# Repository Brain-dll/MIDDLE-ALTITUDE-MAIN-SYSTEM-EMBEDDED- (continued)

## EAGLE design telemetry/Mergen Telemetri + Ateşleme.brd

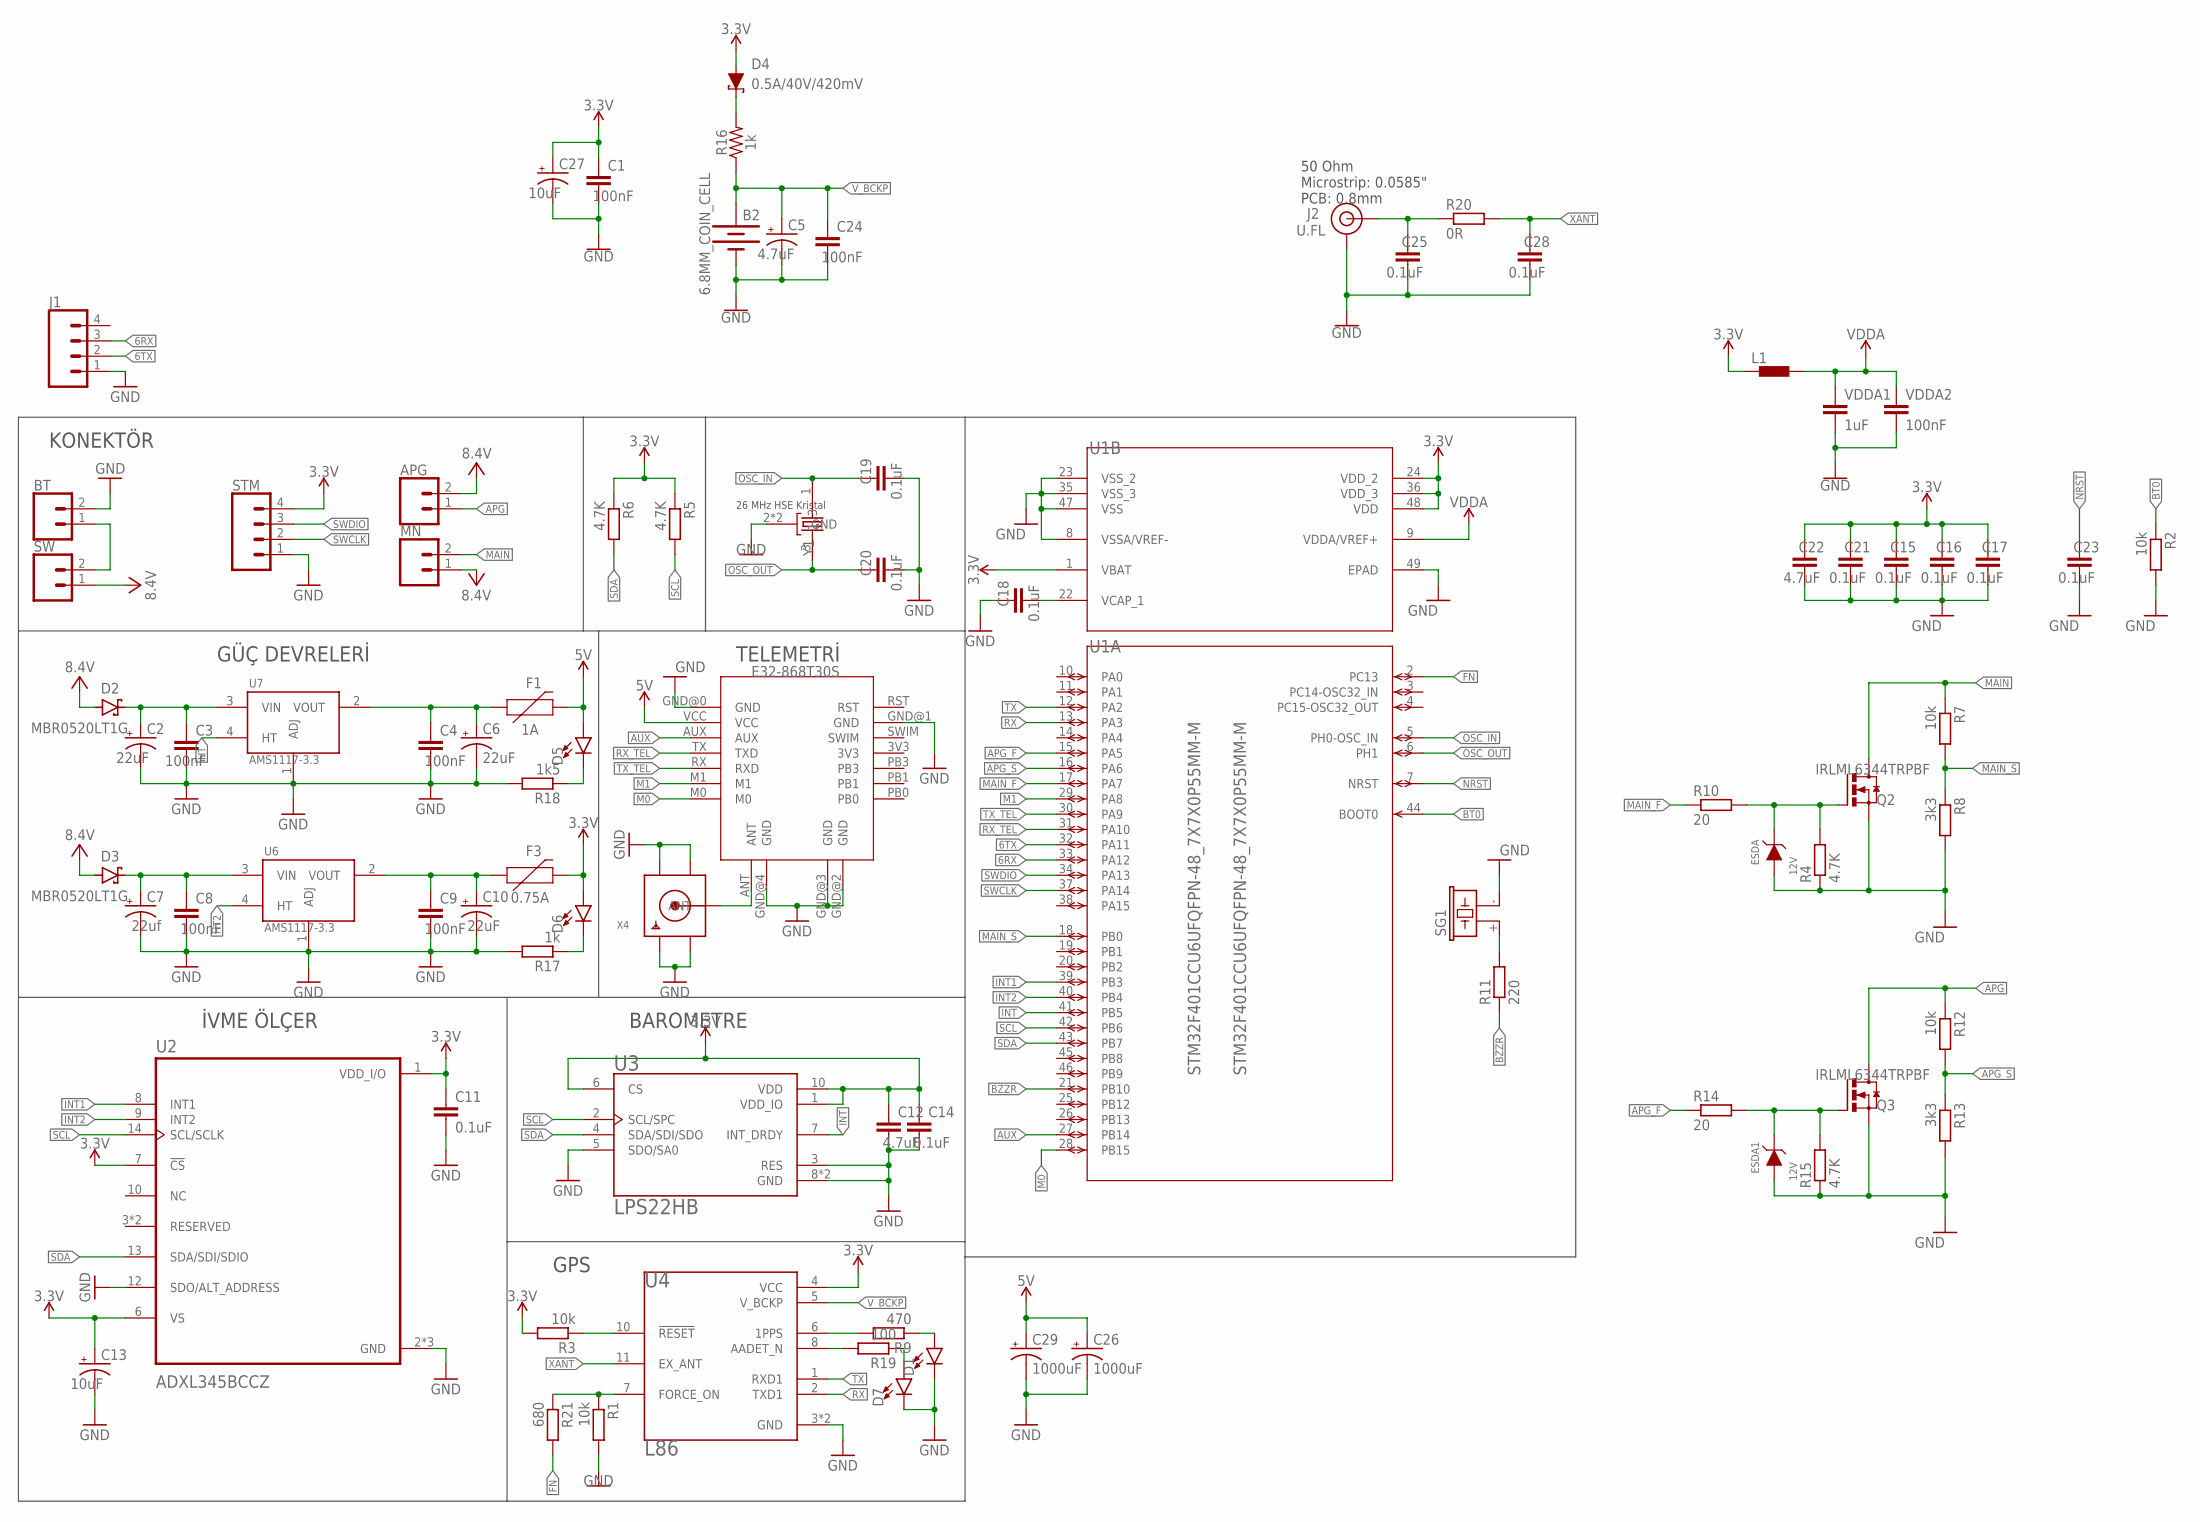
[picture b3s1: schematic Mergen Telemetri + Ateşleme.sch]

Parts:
APG: CONN_02POLAR; MOLEX-1X2
B2: 6.8MM_COIN_CELL; BATTCON-6.8MM
BT: CONN_02POLAR; MOLEX-1X2
C1, C3, C4, C8, C9, C24: 100nF; C0402K
C2, C6, C10: 22uF; R/2012-12W
C5: 4.7uF; R/2012-12W
C7: 22uf; R/2012-12W
C11, C14, C15, C16, C17, C18, C19, C20, C21, C23, C25, C28: 0.1uF; C0402K
C12, C22: 4.7uF; C0402K
C13, C27: 10uF; R/2012-12W
C26, C29: 1000uF; 150CLZ-1010
D1, D5, D6, D7: LED0603; LED-0603
D2, D3: MBR0520LT1G; SODFL3718X115
D4: 0.5A/40V/420mV; SOD-323
ESDA, ESDA1: 12V; WE-TVSP_DO-214AC_UNIDIRECTIONAL
F1: 1A; 1206
F3: 0.75A; 1206
J1: CONN_04JST-PTH-VERT; JST-4-PTH-VERT
J2: U.FL
L1: BLM15HB221SN1; 0402
MN: CONN_02POLAR; MOLEX-1X2
Q2, Q3: IRLML6344TRPBF; SOT23
R1, R2, R3, R7, R12: 10k; R0402
R4, R5, R6, R15: 4.7K; R0402
R8, R13: 3k3; R0402
R9: 470; R0402
R10, R14: 20; R0402
R11: 220; R0402
R16: 1k; 0603
R17: 1k; R0402
R18: 1k5; R0402
R19: 100; R0402
R20: 0R; R0402
R21: 680; R0402
SG1: F/CM12P
STM: CONN_04; 1X04
SW: CONN_02POLAR; MOLEX-1X2
U1: STM32F401CCU6UFQFPN-48_7X7X0P55MM-M; UFQFPN-48_7X7X0P55MM-M
U2: ADXL345BCCZ; PQFN80P300X500X100-14N
U3: LPS22HB; LGA10R50P2X3_200X200X80
U4: L86; XCVR_L86
U5: E32-868T30S
U6, U7: AMS1117-3.3; SOT229P700X180-4N
VDDA1: 1uF; 0603
VDDA2: 100nF; 0603
X4: SMACONNECTOR; SMA90_DIP
Y1: ABM3B-26.000MHZ-10-1-U-T; OSCCC500X320X110-4N

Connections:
3.3V: C1.1, C11.1, C12.1, C13.+, C14.1, C15.1, C16.1, C17.1, C21.1, C22.1, C27.+, D4.A, D6.A, F3.2, L1.1, R3.2, R5.1, R6.1, STM.4, U1.1 (VBAT), U1.24 (VDD_2), U1.36 (VDD_3), U1.48 (VDD), U2.1 (VDD_I/O), U2.6 (VS), U2.7 (!CS), U3.1 (VDD_IO), U3.6 (CS), U3.10 (VDD), U4.4 (VCC)
5V: C26.+, C29.+, D5.A, F1.2, U5.VCC
6RX: J1.3, U1.33 (PA12)
6TX: J1.2, U1.32 (PA11)
APG: APG.1, Q3.3 (D), R12.1
APG_F: R14.1, U1.15 (PA5)
APG_S: R12.2, R13.1, U1.16 (PA6)
AUX: U1.27 (PB14), U5.AUX
BT0: R2.1, U1.44 (BOOT0)
BZZR: R11.1, U1.21 (PB10)
FN: R21.2, U1.2 (PC13)
GND: B2.-, BT.2, C1.2, C2.-, C3.2, C4.2, C5.-, C6.-, C7.-, C8.2, C9.2, C10.-, C11.2, C12.2, C13.-, C14.2, C15.2, C16.2, C17.2, C18.1, C19.2, C20.2, C21.2, C22.2, C23.2, C24.2, C25.2, C26.-, C27.-, C28.2, C29.-, D1.C, D7.C, ESDA.2 (A), ESDA1.2 (A), J1.1, J2.1 (GND), J2.2 (GND), Q2.2 (S), Q3.2 (S), R1.2, R2.2, R4.1, R8.2, R13.2, R15.1, R17.2, R18.2, SG1.- (2), STM.1, U1.8 (VSSA/VREF-), U1.23 (VSS_2), U1.35 (VSS_3), U1.47 (VSS), U1.49 (EPAD), U2.2 (GND), U2.4 (GND), U2.5 (GND), U2.12 (SDO/ALT_ADDRESS), U3.3 (RES), U3.5 (SDO/SA0), U3.8 (GND), U3.9 (GND), U4.3 (GND), U4.12 (GND), U5.GND@0 (GND), U5.GND@1 (GND), U5.GND@2 (GND), U5.GND@3 (GND), U5.GND@4 (GND), U6.1 (ADJ), U7.1 (ADJ), VDDA1.2, VDDA2.2, X4.GND1, X4.GND2, X4.GND3, X4.GND4, Y1.2 (GND), Y1.4 (GND)
HT: U7.4 (HT)
HT2: U6.4 (HT)
INT: U1.41 (PB5), U3.7 (INT_DRDY)
INT1: U1.39 (PB3), U2.8 (INT1)
INT2: U1.40 (PB4), U2.9 (INT2)
M0: U1.28 (PB15), U5.M0
M1: U1.29 (PA8), U5.M1
MAIN: MN.2, Q2.3 (D), R7.1
MAIN_F: R10.1, U1.17 (PA7)
MAIN_S: R7.2, R8.1, U1.18 (PB0)
unnamed: C2.+, C3.1, D2.1 (C), U7.3 (VIN)
unnamed: C7.+, C8.1, D3.1 (C), U6.3 (VIN)
unnamed: R3.1, U4.10 (!RESET)
unnamed: C4.1, C6.+, F1.1, U7.2 (VOUT)
unnamed: C9.1, C10.+, F3.1, U6.2 (VOUT)
unnamed: ESDA1.1 (C), Q3.1 (G), R14.2, R15.2
unnamed: U5.ANT, X4.ANTENNA (ANT)
unnamed: R11.2, SG1.+ (1)
unnamed: BT.1, SW.2
unnamed: R9.2, U4.6 (1PPS)
unnamed: D1.A, R9.1
unnamed: D4.C, R16.2
unnamed: ESDA.1 (C), Q2.1 (G), R4.2, R10.2
unnamed: D5.C, R18.1
unnamed: D6.C, R17.1
unnamed: R19.2, U4.8 (AADET_N)
unnamed: D7.A, R19.1
unnamed: C18.2, U1.22 (VCAP_1)
unnamed: C25.1, J2.FEED (SIGNAL), R20.1
unnamed: R1.1, R21.1, U4.7 (FORCE_ON)
NRST: C23.1, U1.7 (NRST)
OSC_IN: C19.1, U1.5 (PH0-OSC_IN), Y1.1
OSC_OUT: C20.1, U1.6 (PH1), Y1.3
RX: U1.13 (PA3), U4.2 (TXD1)
RX_TEL: U1.31 (PA10), U5.TX (TXD)
SCL: R5.2, U1.42 (PB6), U2.14 (SCL/SCLK), U3.2 (SCL/SPC)
SDA: R6.2, U1.43 (PB7), U2.13 (SDA/SDI/SDIO), U3.4 (SDA/SDI/SDO)
SWCLK: STM.2, U1.37 (PA14)
SWDIO: STM.3, U1.34 (PA13)
TX: U1.12 (PA2), U4.1 (RXD1)
TX_TEL: U1.30 (PA9), U5.RX (RXD)
VCC: APG.2, D2.2 (A), D3.2 (A), MN.1, SW.1
VDDA: L1.2, U1.9 (VDDA/VREF+), VDDA1.1, VDDA2.1
V_BCKP: B2.+, C5.+, C24.1, R16.1, U4.5 (V_BCKP)
XANT: C28.1, R20.2, U4.11 (EX_ANT)

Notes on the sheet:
GÜÇ DEVRELERİ
İVME ÖLÇER
BAROMETRE
TELEMETRİ
GPS
KONEKTÖR
26 MHz HSE Kristal
50 Ohm Microstrip: 0.0585" PCB: 0.8mm

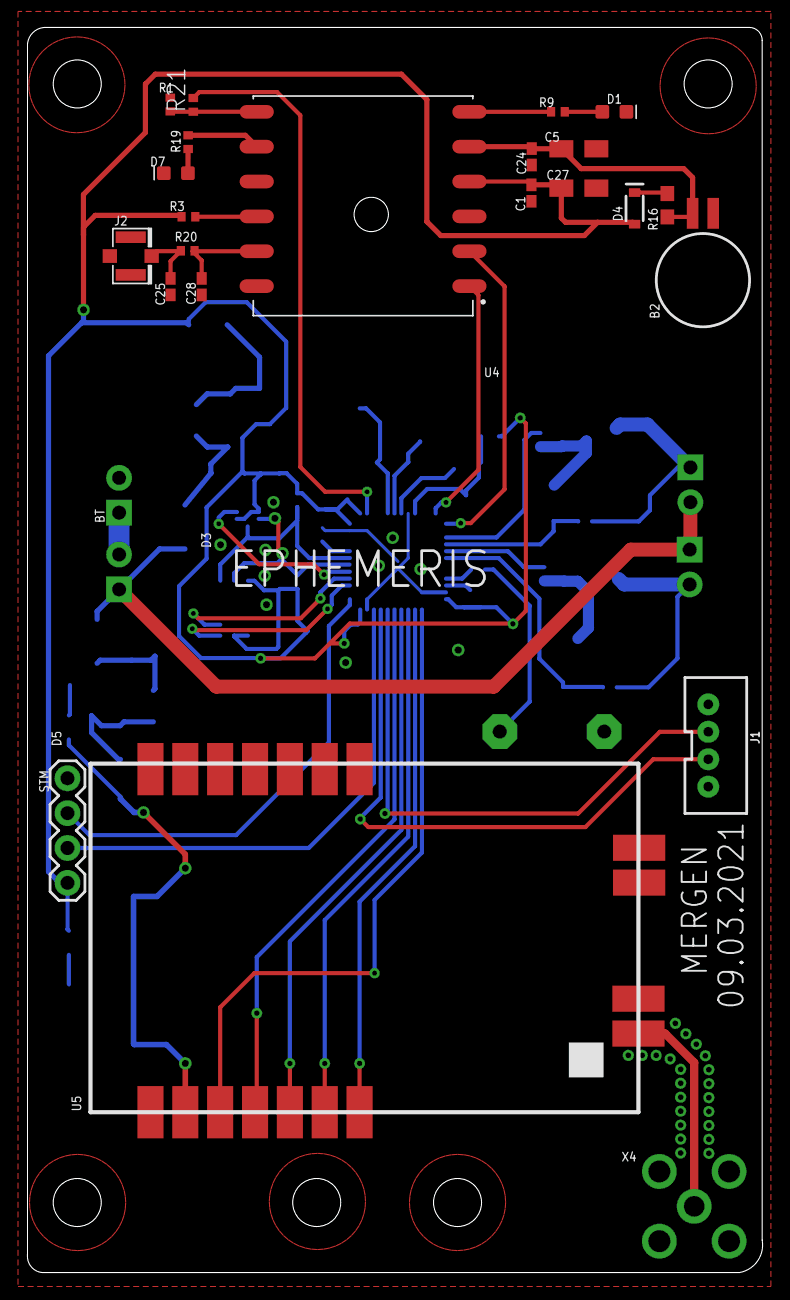
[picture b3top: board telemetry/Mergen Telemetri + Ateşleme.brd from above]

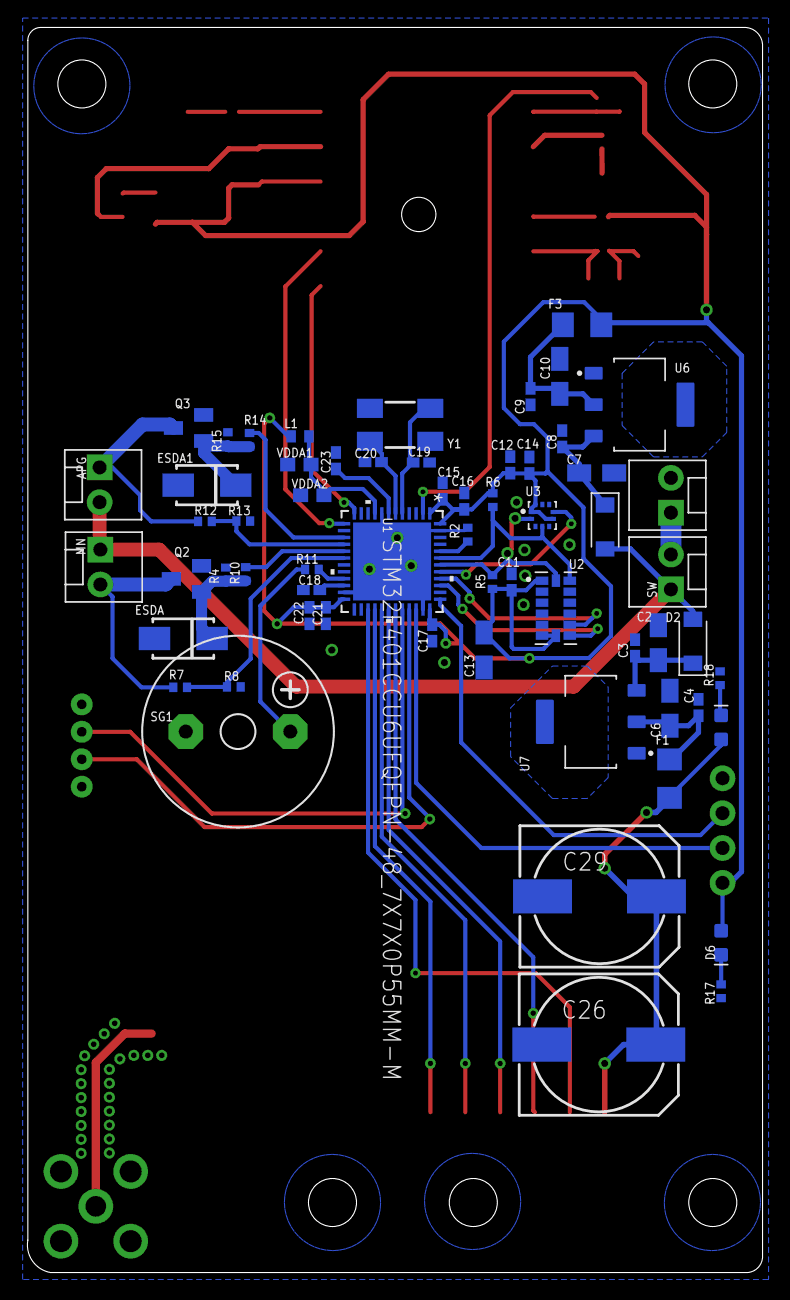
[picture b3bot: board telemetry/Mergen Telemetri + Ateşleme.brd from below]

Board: 2 copper layers, 53.6 x 90.7 mm, 84 parts (61 on the bottom side), 55 nets.

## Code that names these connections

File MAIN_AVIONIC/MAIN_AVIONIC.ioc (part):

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Mcu.Name=STM32F302C(6-8)Tx
Mcu.Package=LQFP48
Mcu.UserName=STM32F302C8Tx
PA0.GPIOParameters=GPIO_Label
PA0.GPIO_Label=M0
PA0.Signal=GPIO_Output
PA1.GPIOParameters=GPIO_Label
PA1.GPIO_Label=M1
PA1.Signal=GPIO_Output
PA10.Mode=I2C
PA10.Signal=I2C2_SDA
PA13.Mode=Serial_Wire
PA13.Signal=SYS_JTMS-SWDIO
PA14.Mode=Serial_Wire
PA14.Signal=SYS_JTCK-SWCLK
PA15.GPIOParameters=GPIO_Label
PA15.GPIO_Label=APOGEE
PA15.Signal=GPIO_Output
PA2.Mode=Asynchronous
PA2.Signal=USART2_TX
PA3.Mode=Asynchronous
PA3.Signal=USART2_RX
PA9.Mode=I2C
PA9.Signal=I2C2_SCL
PB10.Mode=Asynchronous
PB10.Signal=USART3_TX
PB11.Mode=Asynchronous
PB11.Signal=USART3_RX
PB3.GPIOParameters=GPIO_Label
PB3.GPIO_Label=MAIN
PB3.Signal=GPIO_Output
PB6.Mode=Asynchronous
PB6.Signal=USART1_TX
PB7.Mode=Asynchronous
PB7.Signal=USART1_RX
PC13.GPIOParameters=GPIO_Label
PC13.GPIO_Label=BUZZER
PC13.Signal=GPIO_Output
PF0-OSC_IN.Mode=HSE-External-Oscillator
PF0-OSC_IN.Signal=RCC_OSC_IN
PF1-OSC_OUT.Mode=HSE-External-Oscillator
PF1-OSC_OUT.Signal=RCC_OSC_OUT
RCC.HSEPLLFreq_Value=8000000
RCC.HSE_VALUE=8000000
RCC.SYSCLKFreq_VALUE=72000000
RCC.SYSCLKSourceVirtual=RCC_SYSCLKSOURCE_PLLCLK
board=custom

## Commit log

2021-03-08 Telemetry V1.0.0 was completed
2021-03-08 Some modification was maken on the LPS22HB and ADXL345
2021-03-10 Routes were be extended
2021-03-10 LOGO was uploaded
2021-03-14 Extra polygon was added for methal distance and 1x4 JST connector was added for payload
2021-03-24 System was redesigned with new controller and sensors
2021-03-26 New version of boards with new controller was designed
2021-03-28 Connector was changed and Preparing first order
2021-04-03 Polygon witdh was increased IMPORTANT
2021-04-03 Polygon 15 mils
2021-04-06 NMOS trace was be expanded and creating 1206 package version was tried
2021-04-08 packages was modified according to stock situation
2021-04-19 Some modification was done
2021-05-03 Component name locations was arranged
2021-06-02 Update was unsuccesfull
2021-06-30 Documents were redesigned and VDDA cap value was cganed
2021-07-05 5V lineer regülator was added for ignition outputs
2021-07-05 Regulator was added for e match
2021-07-07 Regulator name was changed as 5.0
2021-08-08 Algorithm and Software was added
2021-08-15 Sofware was updated
2021-08-31 last updates was completed, Ready for flying
2021-09-17 Systems are stable
